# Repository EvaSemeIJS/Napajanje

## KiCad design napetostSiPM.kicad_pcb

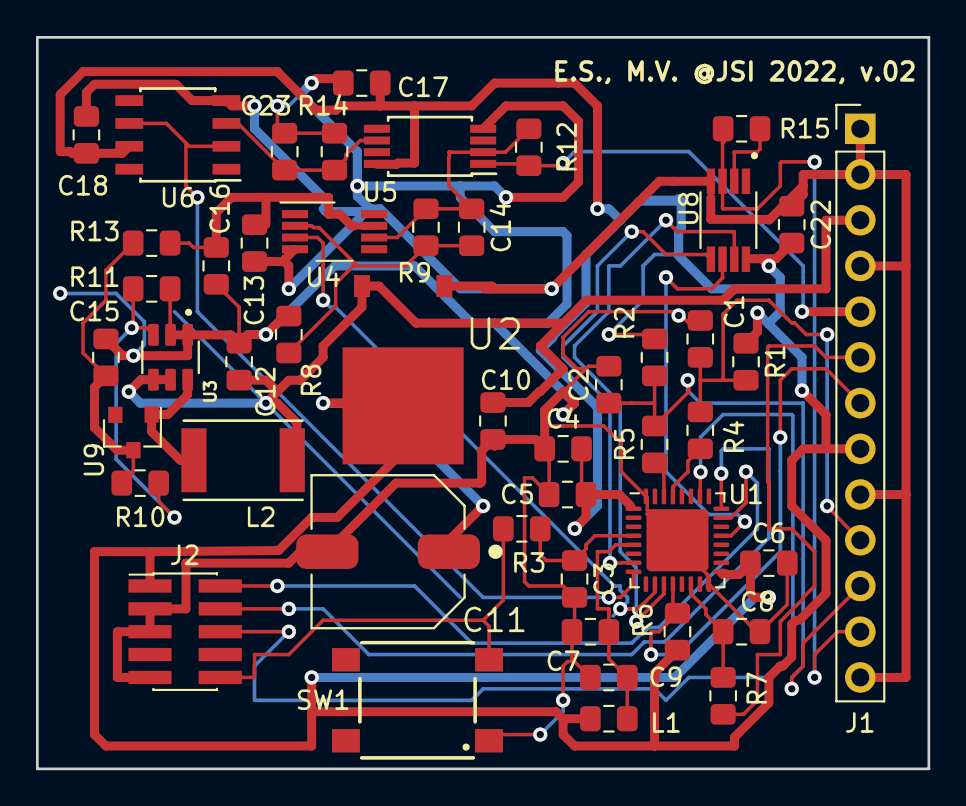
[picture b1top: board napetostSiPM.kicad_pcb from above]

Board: 2 copper layers, 49.5 x 40.6 mm, 48 parts (0 on the bottom side), 31 nets.

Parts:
C1, C2: 0 pF; C_0805_2012Metric_Pad1.15x1.40mm_HandSolder
C3, C5, C6, C8, C13, C14, C17, C18, C22: 100 nF; C_0805_2012Metric_Pad1.15x1.40mm_HandSolder
C4, C12: 4.7 μF; C_0805_2012Metric_Pad1.15x1.40mm_HandSolder
C7, C23: 10 nF; C_0805_2012Metric_Pad1.15x1.40mm_HandSolder
C9, C15, C16: 1 μF; C_0805_2012Metric_Pad1.15x1.40mm_HandSolder
C10: 10 μF; C_0805_2012Metric_Pad1.15x1.40mm_HandSolder
C11: 100 μF; CAPE830X690N
J1: Conn_01x13_Male; PinHeader_1x13_P2.54mm_Vertical
J2: Conn_ARM_JTAG_SWD_10; PinHeader_2x05_P1.27mm_Vertical_SMD
L1: L_Core_Ferrite_Small; L_0805_2012Metric_Pad1.15x1.40mm_HandSolder
L2: 47 μH; Wurth_Electronics-74451147-Manufacturer_Recommended
R1, R2, R7, R8: 10 kΩ; R_0805_2012Metric_Pad1.15x1.40mm_HandSolder
R3: 470 Ω; R_0805_2012Metric_Pad1.15x1.40mm_HandSolder
R4, R5, R13: 100 Ω; R_0805_2012Metric_Pad1.15x1.40mm_HandSolder
R6: 4.7 kΩ; R_0805_2012Metric_Pad1.15x1.40mm_HandSolder
R9: 100 kΩ; R_0805_2012Metric_Pad1.15x1.40mm_HandSolder
R10: 1.2 MΩ; R_0805_2012Metric_Pad1.15x1.40mm_HandSolder
R11: 47 kΩ; R_0805_2012Metric_Pad1.15x1.40mm_HandSolder
R12: 4.7 Ω; R_0805_2012Metric_Pad1.15x1.40mm_HandSolder
R14: 470 kΩ; R_0805_2012Metric_Pad1.15x1.40mm_HandSolder
R15: 3.9 kΩ; R_0805_2012Metric_Pad1.15x1.40mm_HandSolder
SW1: SW_Push; 430182050816
U1: STM32L432KBUx; QFN-32-1EP_5x5mm_P0.5mm_EP3.45x3.45mm
U2: TLV1117-33IDCY; TO228P970X238-3N
U3: MAX5026; SOT95P280X145-6N
U4: OPA196xDBV; VSSOP-8_3.0x3.0mm_P0.65mm
U5: INA168; TSSOP-8_4.4x3mm_P0.65mm
U6: OPA340UA; SOIC-8_3.9x4.9mm_P1.27mm
U8: MAX6682; SOP65P490X110-8N
U9: ZHCS500; SOT-23-dioda

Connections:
/+3.3V: C4.2, C5.2, C6.1, C11.1, C17.1, C18.1, C22.2, J1.8, J2.1, L1.1, R1.1, R2.2, R6.2, U1.1, U1.17, U2.2, U5.8, U6.7, U8.8
/+5V: C10.1, C12.1, J1.3, L2.2, U2.3, U3.4, U3.5
/ANALOG_T: J1.6, R7.1
/BIAS: J1.5, R12.1, U5.1
/BIAS/MAX32V: C13.1, C16.1, R13.1, U4.7
/CURRENT: U1.8, U6.2, U6.6
/DAC: U1.10, U4.3
/DIGITAL_T: J1.7, R6.1, U1.12
/GND: C1.1, C2.2, C3.2, C4.1, C5.1, C6.2, C7.2, C8.2, C9.2, C10.2, C11.2, C12.2, C13.2, C15.2, C16.2, C17.2, C18.2, C22.1, C23.1, J1.1, J1.2, J1.4, J1.9, J1.13, J2.3, J2.5, J2.9, R8.2, R11.2, R14.2, SW1.1, U1.16, U1.32, U1.33, U2.1, U3.1, U3.2, U4.4, U5.4, U6.4, U8.4
/NRST: J2.10, R3.1, SW1.2
/NTC: J1.12, R15.2, U8.3
/SCL: C1.2, J1.10, R1.2, R4.2
/SDA: C2.1, J1.11, R2.1, R5.2
/SWDCLK: J2.4, U1.24
/SWDIO: J2.2, U1.23
/SWO: J2.6, U1.26
/microprocesor/NTC_CS: U1.7, U8.5
/microprocesor/NTC_SCLK: U1.11, U8.7
/microprocesor/NTC_SO: U1.21, U8.6
unnamed: C3.1, R3.2, U1.4
unnamed: C7.1, C9.1, L1.2, U1.5
unnamed: C8.1, R7.2, U1.14
unnamed: C14.1, R9.1, R12.2, U4.6, U5.2
unnamed: C14.2, R8.1, R9.2, U4.2
unnamed: C15.1, R10.1, R13.2, U9.1
unnamed: C23.2, R14.1, U5.6, U6.3
unnamed: L2.1, U3.6, U9.3
unnamed: R4.1, U1.29
unnamed: R5.1, U1.30
unnamed: R10.2, R11.1, U3.3
unnamed: R15.1, U8.2
